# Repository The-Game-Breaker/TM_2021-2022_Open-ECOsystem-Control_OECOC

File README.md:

# TM_2021-2022_Open-ECOsystem-Control_OECOC
Open source ecosystem controller for controlling:
- Terrariums 
- Aquariums 
- Ponds
- Aquaponics
- Greenhouses 
- Etc

It is divided in the following:
- Nodes
- Central server
- Terminal
---
- [TM_2021-2022_Open-ECOsystem-Control_OECOC](#tm_2021-2022_open-ecosystem-control_oecoc)
  - [- Terminal](#--terminal)
  - [Nodes](#nodes)
  - [Central Server](#central-server)
- [Hardware](#hardware)
  - [Nodes](#nodes-1)
      - [Reason of choice](#reason-of-choice)
  - [Central Server](#central-server-1)
      - [Reason of choice](#reason-of-choice-1)
  - [End user terminal](#end-user-terminal)
      - [Reason of choice](#reason-of-choice-2)
  - [Sensors](#sensors)
    - [AHT10](#aht10)
      - [Reason of choice](#reason-of-choice-3)
    - [DS18B20](#ds18b20)
      - [Reason of choice](#reason-of-choice-4)
    - [Reed switches](#reed-switches)
      - [Reason of choice](#reason-of-choice-5)
  - [Power](#power)
    - [Current sensor](#current-sensor)
      - [Reason of choice](#reason-of-choice-6)
  - [Actuators](#actuators)
    - [Relay modules](#relay-modules)
- [Software](#software)
  - [Visual studio code](#visual-studio-code)
  - [Openscad](#openscad)
  - [Fusion360](#fusion360)
  - [Home assistant](#home-assistant)
  - [ESPhome](#esphome)
  - [Node-RED](#node-red)
  - [InfluxDB](#influxdb)
- [Protocols](#protocols)
  - [Wifi](#wifi)
  - [Home Assistant api](#home-assistant-api)
  - [MQTT](#mqtt)
- [Schematics](#schematics)
- [Flowchart](#flowchart)

## Nodes
Nodes are used to read the environmental sensors and communicate the information to the central server. They are also used to control several actuators to influence the environment.

## Central Server
The central server is used to receive data from the the nodes and communicate the information to the the users and other nodes. The central server decides which actions are required to keep the environmental parameters within the required limits.

The server also provides a local and remote platform to view and control the environmental parameters.

# Hardware
## Nodes
The ESP32 formes the bases for the nodes. It is programmed using ESPHome. It provides a platform for the sensors and relays to connect with the central server. The connection between the nodes and sensors is enabled by a carrier board. Pictured below.

On this board the sensors are mounted with modular connectors.

#### Reason of choice
I chose the ESP32 because it is a compact and afordable controller with the needed features and pinout. It also allows for future expansion. 

## Central Server
Raspberry pi with homeassistent, ESPHome, node red.
The raspberry pi acts as a central server and provides a grapical web interface to view and control the connected devices. It also provides a system to program and update the nodes. Finally it provides a Node-RED interface to program and fine-tune the control and automation features.

#### Reason of choice
I chose this platform because I was already partly familiar with it. It is also very flexible and versitile.

## End user terminal
Raspberry pi with touchscreen and homeassistent interface.

#### Reason of choice
I wanted to be able to see the interface when standing near the terrariums so this way I am able to view and control the terrariums easily.

## Sensors
An overvieuw of the various sensors and their uses.

---

### AHT10
The AHT10 will be used to monitor the temperature and humidity.

#### Reason of choice
I chose this sensor because it was a most suitable for this application. It measures essential features like temperature and humidity but it doesn't have unused features like air pressure which doesn't matter in terrarium environments (this would be overkill). Therefore, it is also a lot cheaper than a Bosch BME280 which was my first idea. The sensor is also natively supported in ESPHome.

### DS18B20
The DS18B20 will be used to monitor the temperature of water or very humid environments.

#### Reason of choice
I chose this sensor because it is a well-known sensor that provides reasonable temperature data for its price.

### Reed switches
These are used to monitor if the terrarium doors are opened. If it's opened too long, it sends a notification via home assistant and sounds an alarm.

#### Reason of choice
I chose these because I had them available and they matched for use in my project. It also adds an extra feature to the system that is not typically found in thermostats.

## Power
### Current sensor
The current sensor is used to monitor the power consumption. It also provides the ability to calculate the running costs.

#### Reason of choice
I chose this sensor because it was fairly cheap. However, if I were to do this again, I would integrate a similar sensor on the carrier board pcb. This would make wiring and deploying much easier.

## Actuators
### Relay modules
The relay module is responsible for controlling the various actuators.

]

# Software

## Visual studio code
Visual studio code is used to document and manage the files of the project. Initially it was planned to be used to program the project as well but this turned out to be unnecessary.

I chose it because I'm familiar with it.

## Openscad
Openscad was used to create some of the 3D models such as the DIN mounts. I used a script made by remoteqth.com. Because openscad is code based, it makes it easy to create different models based on the same "source model" simply by using different parameters.

## Fusion360
Fusion360 was used to create some of the more custom models such as the node mainboard mounting plate.

## Home assistant
Home assistant is used as the central server for the OECOC system. It also provides a user interface (UI) for interacting with the OECOC system. Finally it hosts some of the needed software. This way, we have an all-in-one package for controlling and programming the system.

## ESPhome
ESPHome is used as the main programmer for the nodes. Not only does it make it easy to create a new and custom node, it also provides a simple way to update OTA. 
It runs directly on the home assistant server. 

## Node-RED
Node-RED is used as the backbone for dealing with the incoming data and automating actions. I chose it because it is easy to work with and very adaptable. It also runs directly on the home assistant server.

## InfluxDB
I decided to use InfluxDB to log the incoming data to get a better understanding of the temperature flow. At the moment I don't use the captured data for anything besides being able to look at it. This data could become very usefull in newer iterations of the project. InfluxDB was chosen because it is easy to use and is designed to work with timed data.

It also runs on the home assistant server.

# Protocols
## Wifi
Used to communicate between the main server node and web interface clients.

## Home Assistant api
THe home Assistant API is used to communicate with everything on the main server and web interface.

## MQTT
MQTT is not really used but is considered for later intergration.

# Schematics

# Flowchart

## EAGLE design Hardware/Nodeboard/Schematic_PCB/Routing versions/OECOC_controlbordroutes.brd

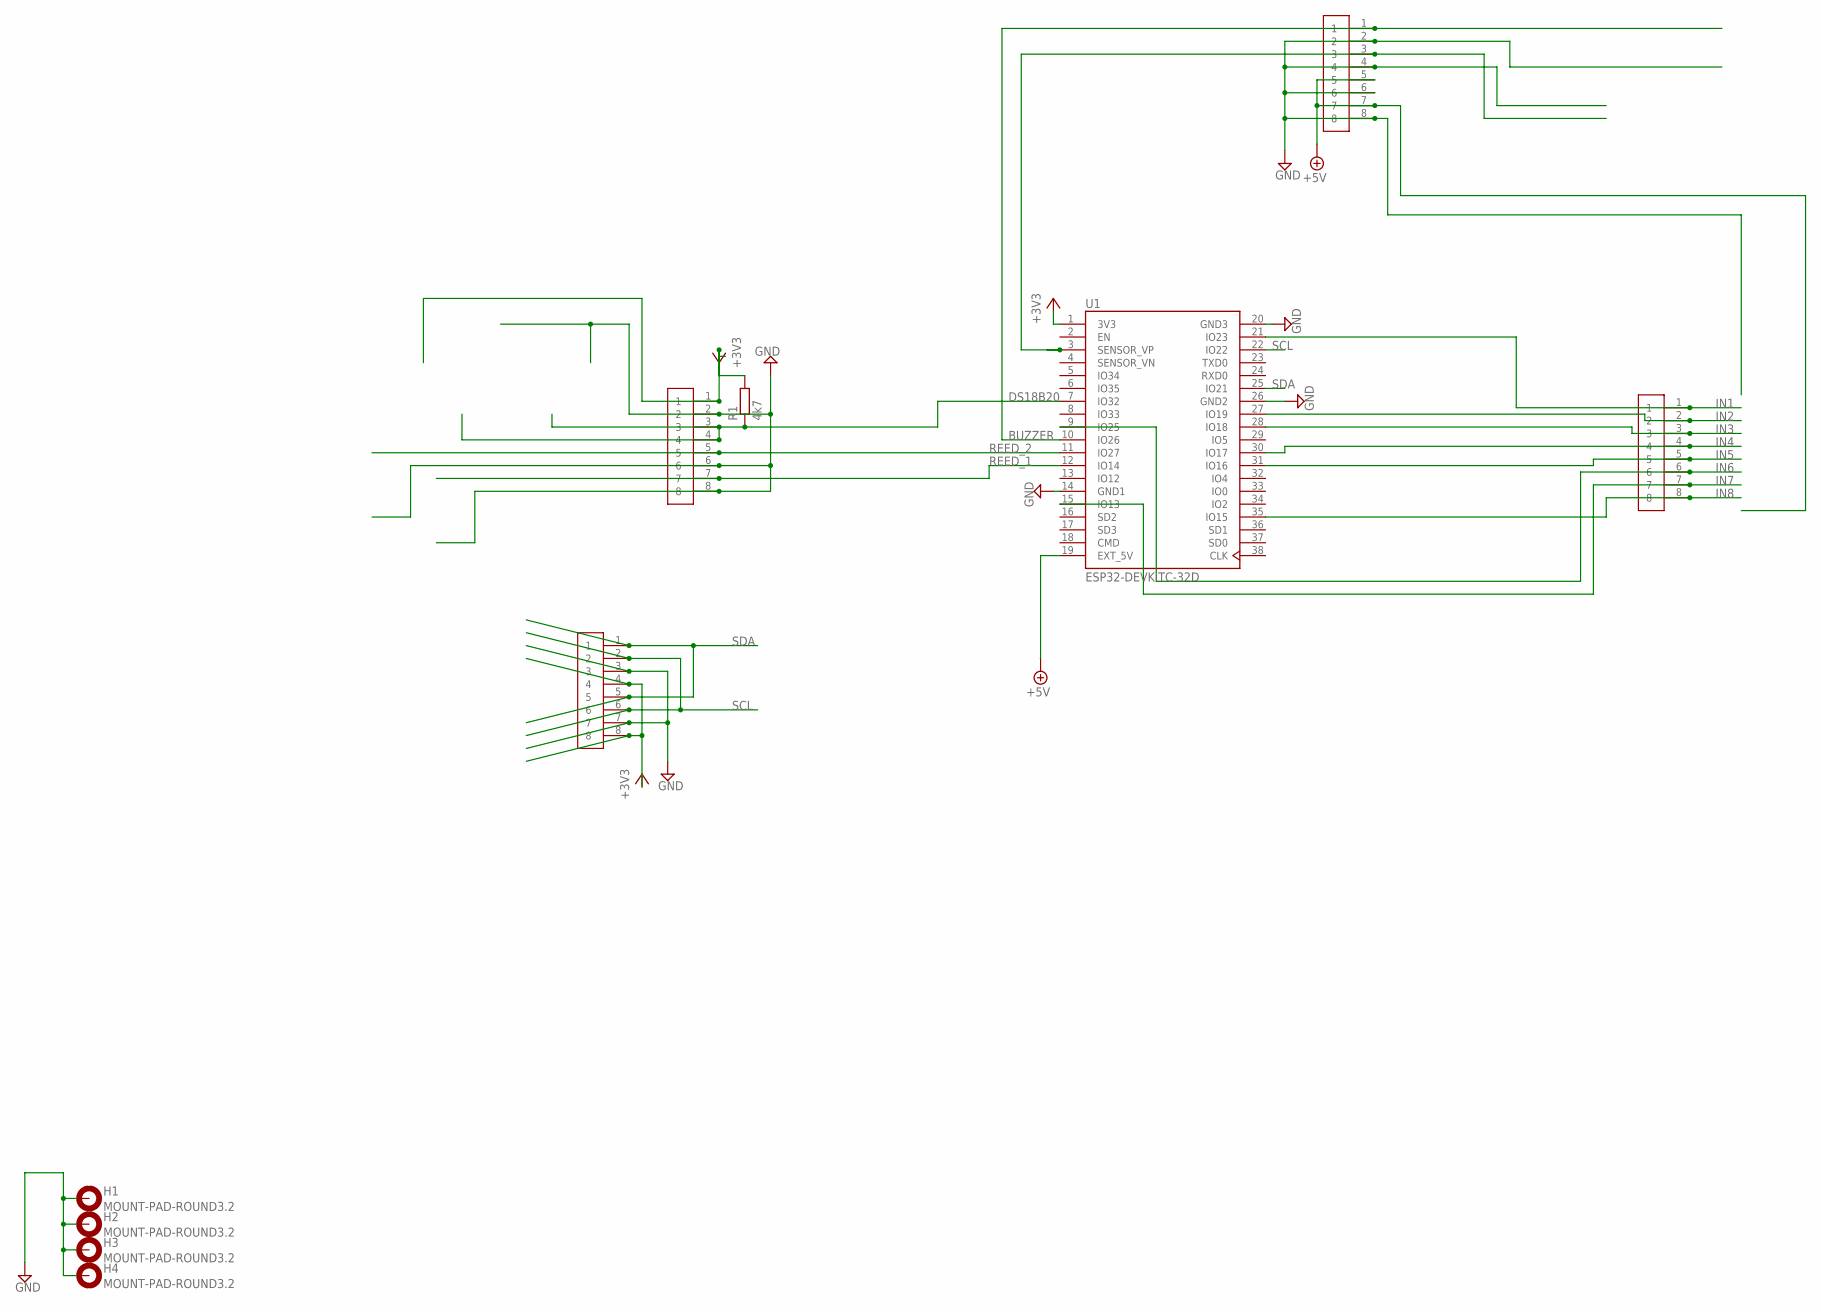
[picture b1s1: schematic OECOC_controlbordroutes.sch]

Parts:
H1, H2, H3, H4: MOUNT-PAD-ROUND3.2; 3,2-PAD
R1: 4k7; 0207/10
U1: ESP32-DEVKITC-32D; MODULE_ESP32-DEVKITC-32D
U$3, U$6, U$7, U$8: PHOENIXCONTACT_PINSTRIP; HDRV8W150P500_1X8_2488X140X1204B

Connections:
+3V3: R1.2, U1.1 (3V3), U$3.4, U$3.8, U$6.1
+5V: U1.19 (EXT_5V), U$8.5, U$8.7
BUZZER: U1.10 (IO26), U$8.1
DS18B20: R1.1, U1.7 (IO32), U$6.3, U$6.4
GND: H1.B3,2, H2.B3,2, H3.B3,2, H4.B3,2, U1.14 (GND1), U1.20 (GND3), U1.26 (GND2), U$3.3, U$3.7, U$6.2, U$6.6, U$6.8, U$8.2, U$8.4, U$8.6, U$8.8
IN1: U1.21 (IO23), U$7.1
IN2: U1.27 (IO19), U$7.2
IN3: U1.28 (IO18), U$7.3
IN4: U1.30 (IO17), U$7.4
IN5: U1.31 (IO16), U$7.5
IN6: U1.9 (IO25), U$7.6
IN7: U1.15 (IO13), U$7.7
IN8: U1.35 (IO15), U$7.8
unnamed: U1.3 (SENSOR_VP), U$8.3
REED_1: U1.12 (IO14), U$6.7
REED_2: U1.11 (IO27), U$6.5
SCL: U1.22 (IO22), U$3.2, U$3.6
SDA: U1.25 (IO21), U$3.1, U$3.5

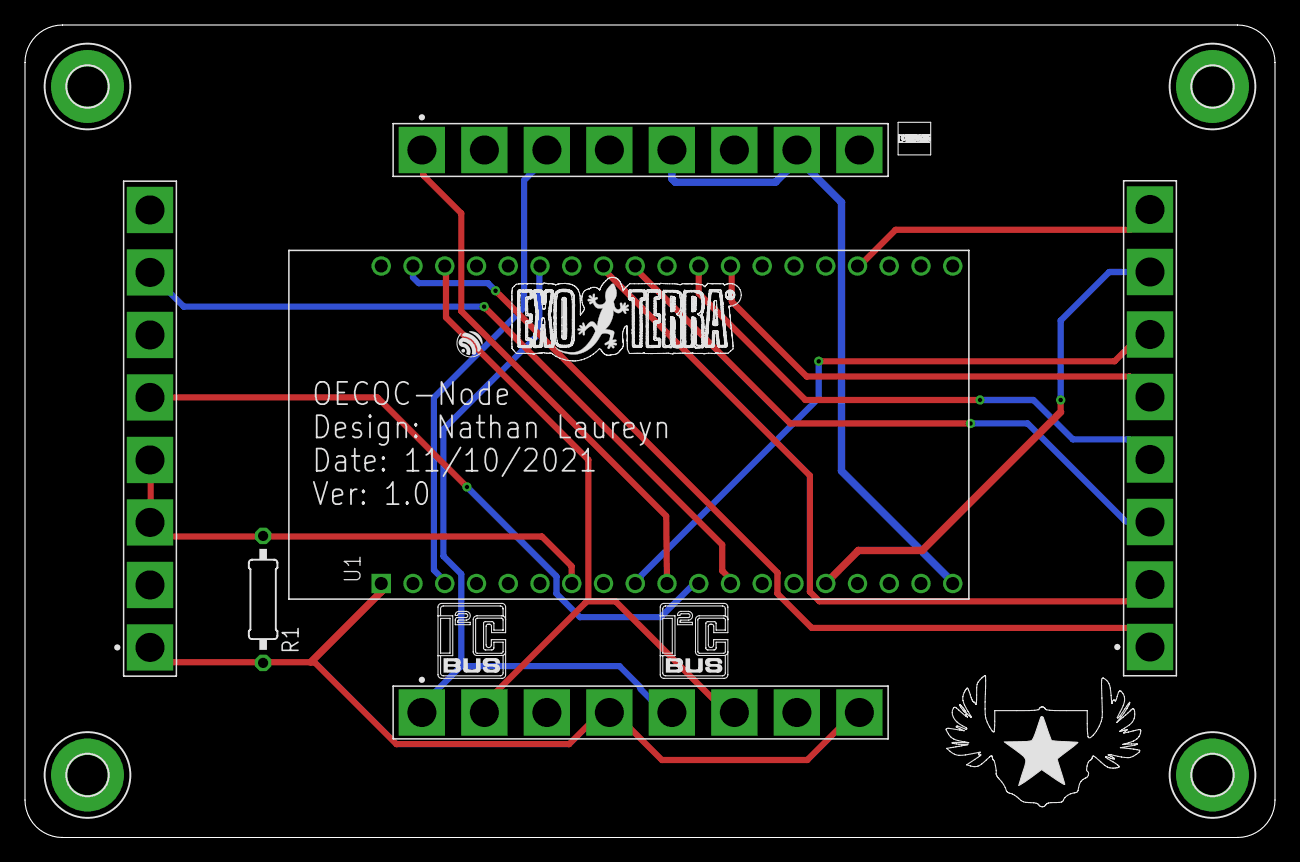
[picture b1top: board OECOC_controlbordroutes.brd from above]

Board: 2 copper layers, 100.0 x 65.0 mm, 16 parts (0 on the bottom side), 18 nets.

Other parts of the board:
U$1: LOGO
U$2, U$4: I2C
U$5: LOGO_EXO-TERRA
U$9: LOGO_ESPRESSIF-SYSTEMS
U$10: LOGO_PHOENIX-CONTACT

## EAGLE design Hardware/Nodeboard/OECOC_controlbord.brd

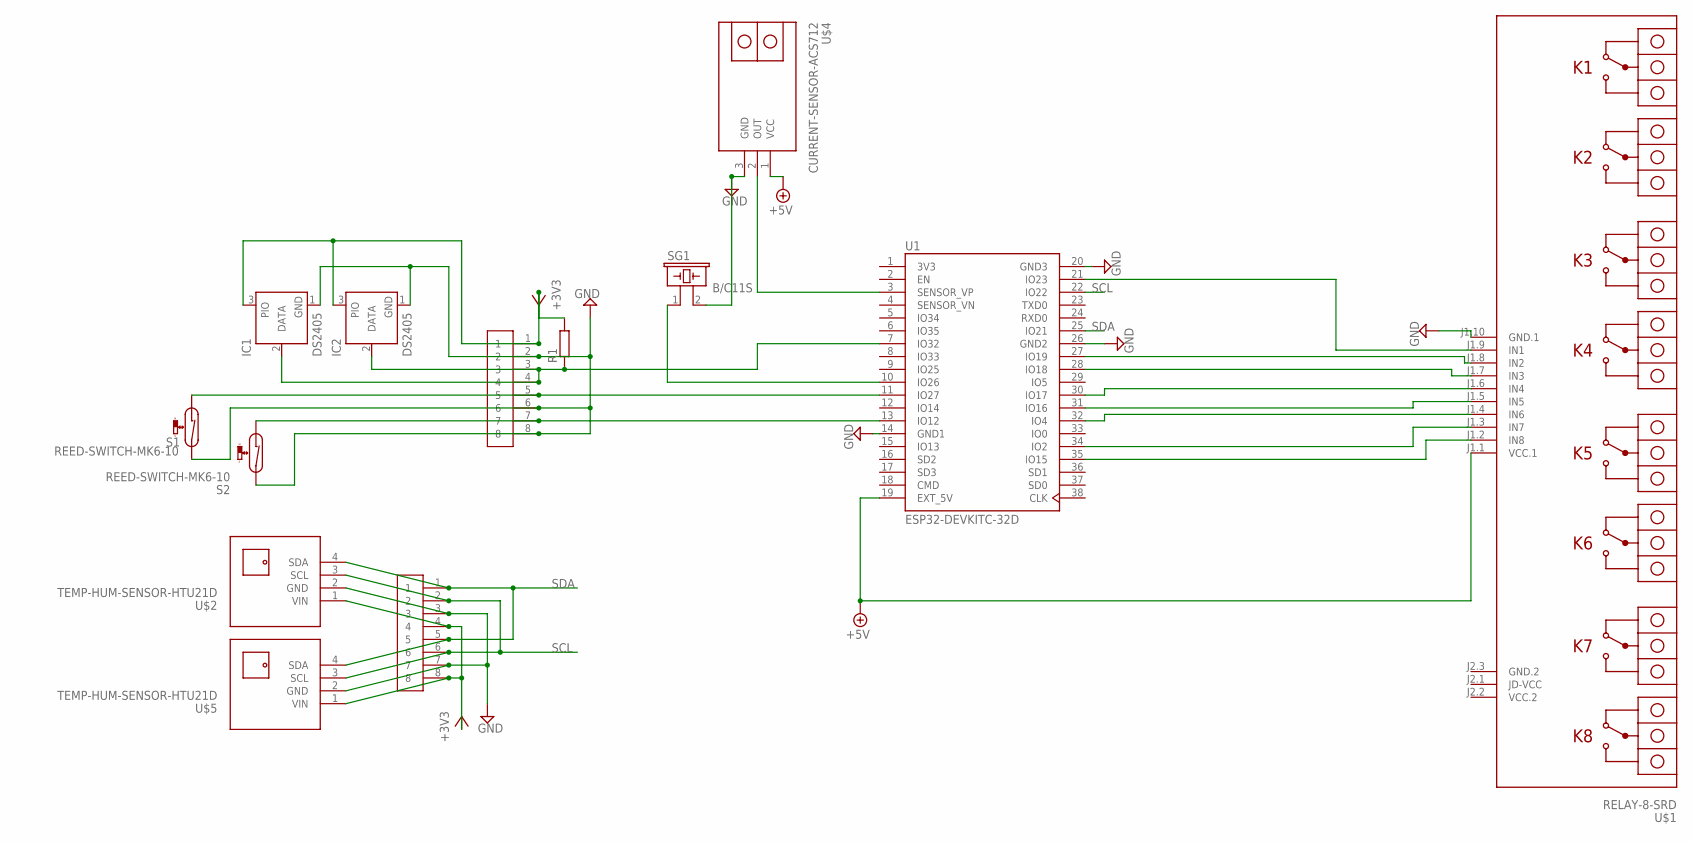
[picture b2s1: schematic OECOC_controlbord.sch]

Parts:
IC1, IC2: DS2405; TO92-
R1: R-EU_0207/10; 0207/10
S1, S2: REED-SWITCH-MK6-10; MK6-10
SG1: B/C11S
U1: ESP32-DEVKITC-32D; MODULE_ESP32-DEVKITC-32D
U$1: RELAY-8-SRD
U$2, U$5: TEMP-HUM-SENSOR-HTU21D
U$3, U$6: PHOENIXCONTACT_PINSTRIP; HDRV8W150P500_1X8_2488X140X1204B
U$4: CURRENT-SENSOR-ACS712

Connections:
3V3: U1.1 (3V3)
+3V3: IC1.3 (PIO), IC2.3 (PIO), R1.2, U$2.1 (VIN), U$3.4, U$3.8, U$5.1 (VIN), U$6.1
+5V: U1.19 (EXT_5V), U$1.J1.1 (VCC.1), U$4.1 (VCC)
GND: IC1.1 (GND), IC2.1 (GND), S1.2, S2.2, SG1.2, U1.14 (GND1), U1.20 (GND3), U1.26 (GND2), U$1.J1.10 (GND.1), U$2.2 (GND), U$3.3, U$3.7, U$4.3 (GND), U$5.2 (GND), U$6.2, U$6.6, U$6.8
GND.2: U$1.J2.3 (GND.2)
unnamed: U1.3 (SENSOR_VP), U$4.2 (OUT)
unnamed: U1.32 (IO4), U$1.J1.4 (IN6)
unnamed: U1.31 (IO16), U$1.J1.5 (IN5)
unnamed: U1.30 (IO17), U$1.J1.6 (IN4)
unnamed: U1.28 (IO18), U$1.J1.7 (IN3)
unnamed: U1.35 (IO15), U$1.J1.2 (IN8)
unnamed: U1.34 (IO2), U$1.J1.3 (IN7)
unnamed: U1.27 (IO19), U$1.J1.8 (IN2)
unnamed: U1.21 (IO23), U$1.J1.9 (IN1)
unnamed: S1.1, U1.11 (IO27), U$6.5
unnamed: SG1.1, U1.10 (IO26)
unnamed: IC1.2 (DATA), IC2.2 (DATA), R1.1, U1.7 (IO32), U$6.3, U$6.4
unnamed: S2.1, U1.13 (IO12), U$6.7
SCL: U1.22 (IO22), U$2.3 (SCL), U$3.2, U$3.6, U$5.3 (SCL)
SDA: U1.25 (IO21), U$2.4 (SDA), U$3.1, U$3.5, U$5.4 (SDA)
VCC.2: U$1.J2.2 (VCC.2)

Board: 2 copper layers, 13 parts (0 on the bottom side), 18 nets, no tracks yet.

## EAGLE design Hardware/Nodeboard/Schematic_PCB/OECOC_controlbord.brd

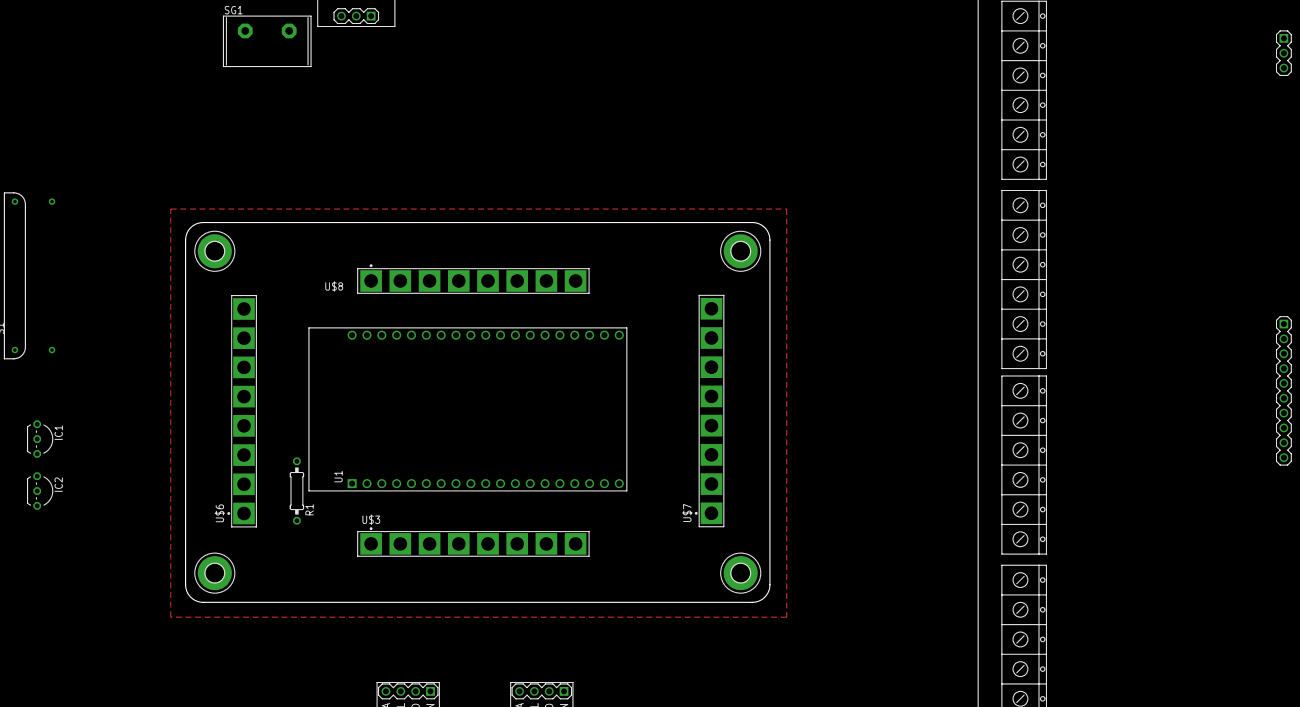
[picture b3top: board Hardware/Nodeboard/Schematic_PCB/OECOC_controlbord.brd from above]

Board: 2 copper layers, 100.0 x 65.0 mm, 19 parts (1 on the bottom side), 18 nets, no tracks yet.

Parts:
H1, H2, H3, H4: MOUNT-PAD-ROUND3.2; 3,2-PAD
IC1, IC2: DS2405; TO92-
R1: 0207/10
S1, S2: REED-SWITCH-MK6-10; MK6-10
SG1: B/C11S
U1: ESP32-DEVKITC-32D; MODULE_ESP32-DEVKITC-32D
U$1: RELAY-8-SRD
U$2, U$5: TEMP-HUM-SENSOR-HTU21D
U$3, U$6, U$7, U$8: PHOENIXCONTACT_PINSTRIP; HDRV8W150P500_1X8_2488X140X1204B
U$4: CURRENT-SENSOR-ACS712

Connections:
+3V3: IC1.3, IC2.3, R1.2, U$2.1, U$3.4, U$3.8, U$5.1, U$6.1
+5V: U1.19, U$1.J1.1, U$8.5, U$8.7
BUZZER: SG1.1, U1.10, U$8.1
DS18B20: IC1.2, IC2.2, R1.1, U1.7, U$6.3, U$6.4
GND: H1.B3,2, H2.B3,2, H3.B3,2, H4.B3,2, IC1.1, IC2.1, S1.2, S2.2, SG1.2, U1.14, U1.20, U1.26, U$1.J1.10, U$2.2, U$3.3, U$3.7, U$4.3, U$5.2, U$6.2, U$6.6, U$6.8, U$8.2, U$8.4, U$8.6, U$8.8
IN1: U1.21, U$1.J1.9, U$7.1
IN2: U1.27, U$1.J1.8, U$7.2
IN3: U1.28, U$1.J1.7, U$7.3
IN4: U1.30, U$1.J1.6, U$7.4
IN5: U1.31, U$1.J1.5, U$7.5
IN6: U1.9, U$1.J1.4, U$7.6
IN7: U1.15, U$1.J1.3, U$7.7
IN8: U1.35, U$1.J1.2, U$7.8
unnamed: U1.3, U$4.2, U$8.3
REED_1: S2.1, U1.12, U$6.7
REED_2: S1.1, U1.11, U$6.5
SCL: U1.22, U$2.3, U$3.2, U$3.6, U$5.3
SDA: U1.25, U$2.4, U$3.1, U$3.5, U$5.4

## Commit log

2021-09-20 test-commit
2021-09-20 remove-test-commit
2021-09-20 add test
2021-09-20 remove-test
2021-09-20 add table of contents
2021-09-20 add workspace file
2021-09-20 add a genral describtion of projects
2021-09-20 changed to the present tense
2021-09-20 add headers to doc
2021-09-20 add main flowchart
2021-09-22 add links
2021-09-22 add uses
2021-09-22 add categories
2021-09-22 add relay module picture
2021-09-26 add items to mainflow
2021-09-26 Add sensors, actuators, software, protocols, flowchart
2021-10-04 add schematic
2021-10-04 add log file
2021-10-04 add extra links
2021-10-04 hw update
2021-10-05 add external sensors and connectors
2021-10-06 add pin distribution
2021-10-07 add buzzer
2021-10-10 changed pins relay
2021-10-10 changed pin relay and reeds
2021-10-11 edit pins relay
2021-10-11 add extra connectors
2021-10-11 add pcb layout
2021-10-11 add labels
2021-10-11 add routing versions
2021-10-11 further pcb development
2021-10-11 finalized pcb and ordered
2021-10-20 add link
2021-11-02 add link+schematic pictures
2021-11-03 add config node and Node-RED
2021-11-03 add images
2021-11-03 add bom
2021-11-03 move schematic and pcb files
2021-11-03 image md test
2021-11-03 image test
2021-11-03 add 3d files
2021-11-03 add readme's
2021-11-03 changed map name
2021-11-03 Add photos and doc
2021-11-03 add doc
2021-11-04 further doc and add how to file
2021-11-04 add step 1 and 2
2021-11-04 add dashboard_config
2021-11-04 improvements
2021-11-04 add hardware section and esphome section
2021-11-05 add instructions
2021-11-05 add bom excel file
2021-11-05 further documentation
2021-11-08 add homeassistant config
2021-11-08 add hassos backup
2023-02-21 Update esphome conf yaml + remove climate feature for now

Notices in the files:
parts and their libraries:
diy-modules: Released under the Creative Commons Attribution 4.0 International License: http://creativecommons.org/licenses/by/4.0
